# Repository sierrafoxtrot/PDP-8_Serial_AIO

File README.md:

# PDP-8 Serial All-in-One

A W070 compatible serial interface for the original DEC PDP-8, providing both teletype current loop and RS-232 compatible interfaces.

## Background

The original PDP-8 was commonly used with an ASR-33 Teletype connected through a DEC W070 interface. The ASR-33 provided a 110 baud printing terminal together with paper tape punch and reader facilities.

The Australian Computer Museum Society PDP-8 is missing its W070 interface. This project started as a [RetroChallenge 2026/10](https://www.retrochallenge.org/) project to build a practical replacement, while adding an RS-232 interface so the machine can also be used with terminals such as a DECWriter or VT220, or with a modern computer through a USB to RS-232 adaptor.

[RetroChallenge 2026/10 project thread](https://forum.acms.org.au/t/rc2026-10-pdp-8-serial-interface/1152)

## Design goals

* Provide a functional replacement for the serial and current loop functions of the DEC W070.
* Retain support for a period current loop Teletype, including reader enable.
* Provide an RS-232 DCE interface on a DE-9 connector.
* Allow the PDP-8 transmit, receive and reader enable paths to be independently selected between current loop and RS-232.
* Preserve the PDP-8 negative logic interface levels.
* Provide visible TX, RX and Reader Enable status indicators.
* Use straightforward, readily available components and remain practical to diagnose and repair.

There is deliberately no onboard USB interface. A conventional RS-232 interface keeps the board useful with both period equipment and modern USB to RS-232 adaptors. I've compromised on going with the the more 1980's era DE-9 connector to accomodate the screw terminals for the current loop.

## Interfaces

### W070 compatible current loop

The six position terminal block provides the Teletype connections:

| Terminal | Connection |
| ---: | --- |
| 1 | TTI return |
| 2 | TTO |
| 3 | TTI, -15 V |
| 4 | Reader, +10 V |
| 5 | Reader enable |
| 6 | TTO return |

The connections are arranged as three pairs:

* **TTI / keyboard:** 3 (-15 V), 1 (return)
* **TTO / printer:** 2 (TTO), 6 (return)
* **Reader enable:** 4 (+10 V), 5 (enable)

### RS-232

The DE-9 connector is wired as **DCE** and is intended for use with a straight through cable to a DTE terminal or computer. If you are using a USB-RS232 adaptor, it should plug in directly.

| Pin | Function |
| ---: | --- |
| 2 | TX |
| 3 | RX |
| 5 | GND |
| 8 | CTS / Reader Enable |

### Interface selection

Three selector links choose the interface used for the relevant PDP-8 signals:

| Link position | Interface |
| --- | --- |
| 1 to 2 | RS-232 |
| 2 to 3 | Current loop |

### Indicators

* **TX** indicates transmitted SPACE states.
* **RX** indicates received SPACE states.
* **RE** indicates Reader Enable.

## Power

The board uses the supplies already available in the PDP-8:

* +10 V
* -15 V
* GND

A local 78L05 regulator provides the +5 V supply required by the interface logic.

## Design files

The project is designed in [KiCad](https://www.kicad.org/). The repository contains the schematic, PCB layout and associated project files required to reproduce or modify the board.

Before manufacturing a board, check the current revision notes and run KiCad ERC and DRC. As with any interface connected to vintage hardware, verify supply voltages and connector wiring before installation.

## Licence

This hardware design is licensed under the **CERN Open Hardware Licence Version 2, Weakly Reciprocal**.

SPDX-License-Identifier: `CERN-OHL-W-2.0`

See [LICENSE](LICENSE) for the full licence text.

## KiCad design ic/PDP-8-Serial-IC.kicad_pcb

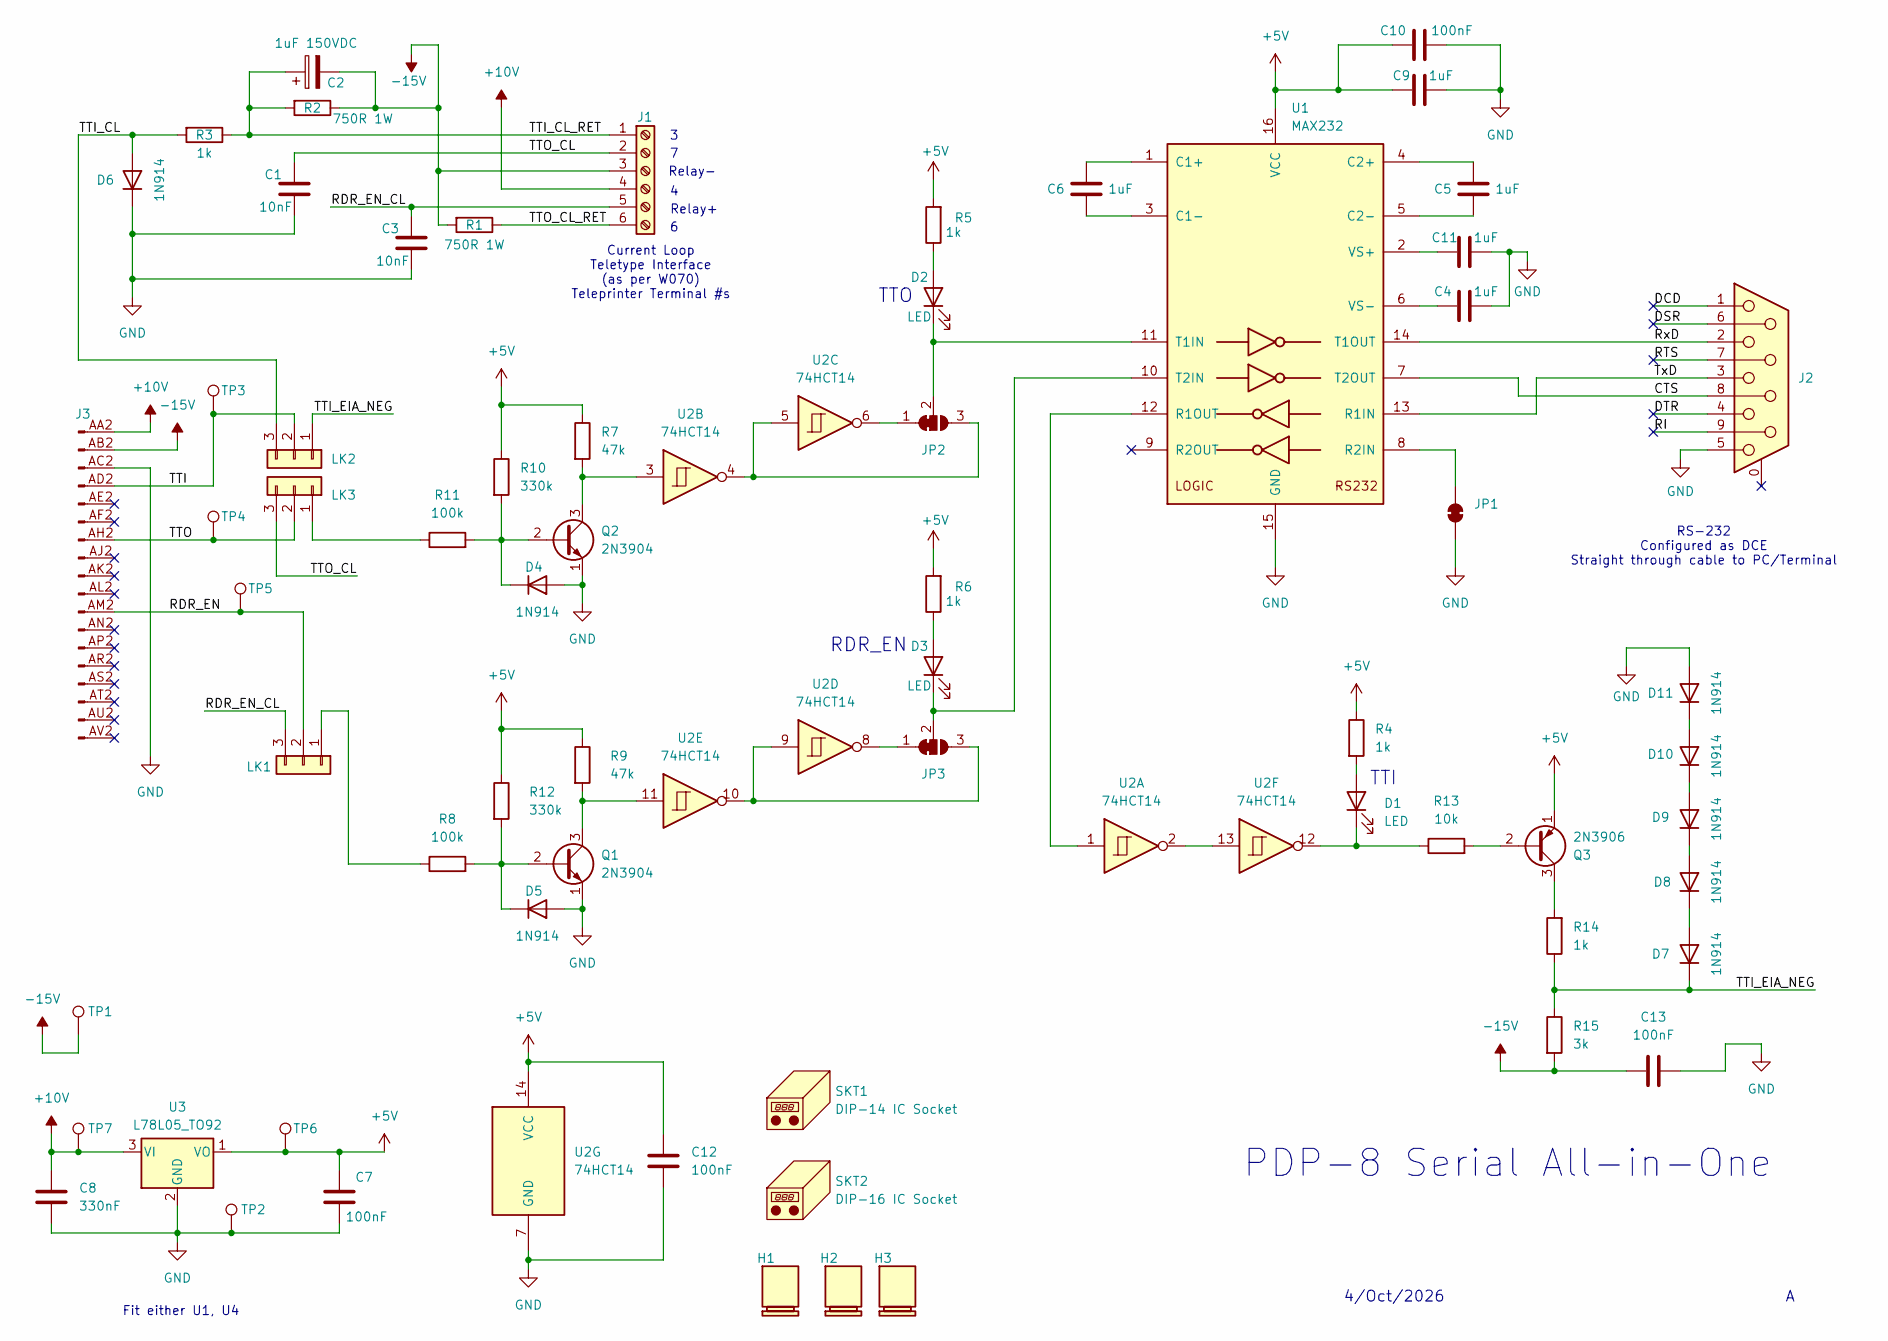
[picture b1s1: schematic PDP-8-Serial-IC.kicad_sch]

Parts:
C1, C3: 10nF; C_Disc_D5.0mm_W2.5mm_P2.50mm; MPN RDER71H103K0K1H03B; Digikey_PN 490-8812-ND
C2: 1uF 150VDC; CP_Axial_L29.0mm_D13.0mm_P35.00mm_Horizontal; MPN MKP1839510254; Digikey_PN 2870-MKP1839510254-ND
C4, C5, C6, C9, C11: 1uF; C_Disc_D5.0mm_W2.5mm_P5.00mm; MPN RDER71H105K2K1H03B; Digikey_PN 490-8816-ND
C7, C10, C12, C13: 100nF; C_Disc_D5.0mm_W2.5mm_P2.50mm; MPN RDER71H104K0S1H03A; Digikey_PN 490-9145-1-ND
C8: 330nF; C_Disc_D5.0mm_W2.5mm_P5.00mm; MPN FA14X7R1H334KNU06; Digikey_PN 445-180408-1-ND
D1, D2, D3: LED; LED_D3.0mm; MPN LTL1CHKEKNN; Digikey_PN 160-1943-ND
D4, D5, D6, D7, D8, D9, D10, D11: 1N914; D_DO-35_SOD27_P7.62mm_Horizontal; MPN 1N914B; Digikey_PN 1N914B-ND
H1, H2, H3: Jumper_Shunt; MPN QPC02SXGN-RC; DigiKey_PN S9337-ND
J1: Screw_Terminal_01x06; PhoenixContact_MC_1,5_6-G-3.5_1x06_P3.50mm_Horizontal
J2: DE9_Socket_MountingHoles; DSUB-9_Pins_Horizontal_P2.77x2.84mm_EdgePinOffset7.70mm_Hou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; MPN A-DF 09 A/KG-T2S; Digikey_PN AE10921-ND
J3: FlipChip_01x18; DEC_single_short_holeless
JP1: SolderJumper_2_Bridged; SolderJumper-2_P1.3mm_Bridged2Bar_RoundedPad1.0x1.5mm
JP2, JP3: SolderJumper_3_Bridged12; SolderJumper-3_P1.3mm_Bridged2Bar12_RoundedPad1.0x1.5mm_Num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
LK1, LK2, LK3: Conn_01x03; PinHeader_1x03_P2.54mm_Vertical; MPN PREC003SAAAN-RC; Digikey_PN S1012EC-03-ND
Q1, Q2: 2N3904; TO-92_Inline; MPN 2N3904BU; Digikey_PN 2N3904FS-ND
Q3: 2N3906; TO-92_Inline; MPN 2N3906BU; Digikey_PN 2N3906FS-ND
R1, R2: 750R 1W; R_Axial_DIN0414_L11.9mm_D4.5mm_P20.32mm_Horizontal; MPN RSF100JB-73-750R; Digikey_PN 13-RSF100JB-73-750R-ND
R3, R4, R5, R6, R14: 1k; R_Axial_DIN0207_L6.3mm_D2.5mm_P10.16mm_Horizontal; MPN MFR-25FBF52-1K; Digikey_PN 1.00KXBK-ND
R7, R9: 47k; R_Axial_DIN0207_L6.3mm_D2.5mm_P10.16mm_Horizontal; MPN RES 47K OHM 1% 1/4W AXIAL; Digikey_PN MFR-25FBF52-47K-ND
R8, R11: 100k; R_Axial_DIN0207_L6.3mm_D2.5mm_P10.16mm_Horizontal; MPN MFR-25FBF52-100K; Digikey_PN 100KXBK-ND
R10, R12: 330k; R_Axial_DIN0207_L6.3mm_D2.5mm_P10.16mm_Horizontal; MPN MFR-25FBF52-330K; Digikey_PN MFR-25FBF52-330K-ND
R13: 10k; R_Axial_DIN0207_L6.3mm_D2.5mm_P10.16mm_Horizontal; MPN MFR-25FBF52-10K; Digikey_PN 10.0KXBK-ND
R15: 3k; R_Axial_DIN0207_L6.3mm_D2.5mm_P10.16mm_Horizontal; MPN MFR-25FBF52-3K; Digikey_PN 13-MFR-25FBF52-3K-ND
SKT1: DIP-14 IC Socket; MPN A 14-LC-TT; Digikey_PN AE9989-ND
SKT2: DIP-16 IC Socket; MPN A 16-LC-TT; Digikey_PN AE9992-ND
TP1: -15V; TestPoint_Loop_D3.50mm_Drill0.9mm_Beaded
TP2: GND; TestPoint_Loop_D3.50mm_Drill0.9mm_Beaded
TP3: TTI; TestPoint_Loop_D3.50mm_Drill0.9mm_Beaded
TP4: TTO; TestPoint_Loop_D3.50mm_Drill0.9mm_Beaded
TP5: RDR_EN; TestPoint_Loop_D3.50mm_Drill0.9mm_Beaded
TP6: +5V; TestPoint_Loop_D3.50mm_Drill0.9mm_Beaded
TP7: +10V; TestPoint_Loop_D3.50mm_Drill0.9mm_Beaded
U1: MAX232; DIP-16_W7.62mm; MPN MAX232EIN; Digikey_PN 296-27963-5-ND
U2: 74HCT14; DIP-14_W7.62mm; MPN SN74HCT14N; Digikey_PN 296-8394-5-ND
U3: L78L05_TO92; TO-92_Inline; MPN L78L05ACZ; Digikey_PN 497-2952-ND

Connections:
+5V: C7.1, C9.1, C10.1, C12.1, Q3.1 (E), R4.1, R5.2, R6.2, R7.1, R9.1, R10.1, R12.1, TP6.1, U1.16 (VCC), U2.14 (VCC), U3.1 (VO)
+10V: C8.1, J1.4, J3.AA2 (Pin_A), TP7.1, U3.3 (VI)
-15V: C2.2, C13.1, J1.3, J3.AB2 (Pin_B), R1.2, R2.1, R15.2, TP1.1
/CTS: J2.8, U1.7 (T2OUT)
/DCD: J2.1
/DSR: J2.6
/DTR: J2.4
/RDR_EN: J3.AM2 (Pin_M), LK1.2, TP5.1
/RDR_EN_CL: C3.1, J1.5, LK1.3
/RI: J2.9
/RTS: J2.7
/RxD: J2.2, U1.14 (T1OUT)
/TTI: J3.AD2 (Pin_D), LK2.2, TP3.1
/TTI_CL: D6.2 (A), LK2.3, R3.2
/TTI_CL_RET: C2.1, J1.1, R2.2, R3.1
/TTI_EIA_NEG: D7.1 (K), LK2.1, R14.1, R15.1
/TTO: J3.AH2 (Pin_H), LK3.2, TP4.1
/TTO_CL: C1.1, J1.2, LK3.3
/TTO_CL_RET: J1.6, R1.1
/TxD: J2.3, U1.13 (R1IN)
GND: C1.2, C3.2, C4.2, C7.2, C8.2, C9.2, C10.2, C11.2, C12.2, C13.2, D4.2 (A), D5.2 (A), D6.1 (K), D11.2 (A), J2.5, J3.AC2 (Pin_C), JP1.2 (B), Q1.1 (E), Q2.1 (E), TP2.1, U1.15 (GND), U2.7 (GND), U3.2 (GND)
unnamed: D1.2 (A), R4.2
unnamed: D1.1 (K), R13.1, U2.12
unnamed: D2.2 (A), R5.1
unnamed: D2.1 (K), JP2.2 (C), U1.11 (T1IN)
unnamed: D3.2 (A), R6.1
unnamed: D3.1 (K), JP3.2 (C), U1.10 (T2IN)
unnamed: D4.1 (K), Q2.2 (B), R10.2, R11.2
unnamed: D5.1 (K), Q1.2 (B), R8.2, R12.2
unnamed: D7.2 (A), D8.1 (K)
unnamed: D8.2 (A), D9.1 (K)
unnamed: D10.2 (A), D11.1 (K)
unnamed: D9.2 (A), D10.1 (K)
unnamed: JP1.1 (A), U1.8 (R2IN)
unnamed: JP2.1 (A), U2.6
unnamed: JP2.3 (B), U2.4, U2.5
unnamed: JP3.1 (A), U2.8
unnamed: JP3.3 (B), U2.9, U2.10
unnamed: LK1.1, R8.1
unnamed: LK3.1, R11.1
unnamed: Q1.3 (C), R9.2, U2.11
unnamed: Q2.3 (C), R7.2, U2.3
unnamed: Q3.2 (B), R13.2
unnamed: Q3.3 (C), R14.2
unnamed: C6.2, U1.1 (C1+)
unnamed: C6.1, U1.3 (C1-)
unnamed: C5.2, U1.4 (C2+)
unnamed: C5.1, U1.5 (C2-)
unnamed: U1.12 (R1OUT), U2.1
unnamed: C11.1, U1.2 (VS+)
unnamed: C4.1, U1.6 (VS-)
unnamed: U2.2, U2.13

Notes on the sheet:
Relay-
TTI
Relay+
Fit either U1, U4
PDP-8 Serial All-in-One
RS-232 Configured as DCE Straight through cable to PC/Terminal
4/Oct/2026
Current Loop Teletype Interface (as per W070) Teleprinter Terminal #s
RDR_EN
TTO

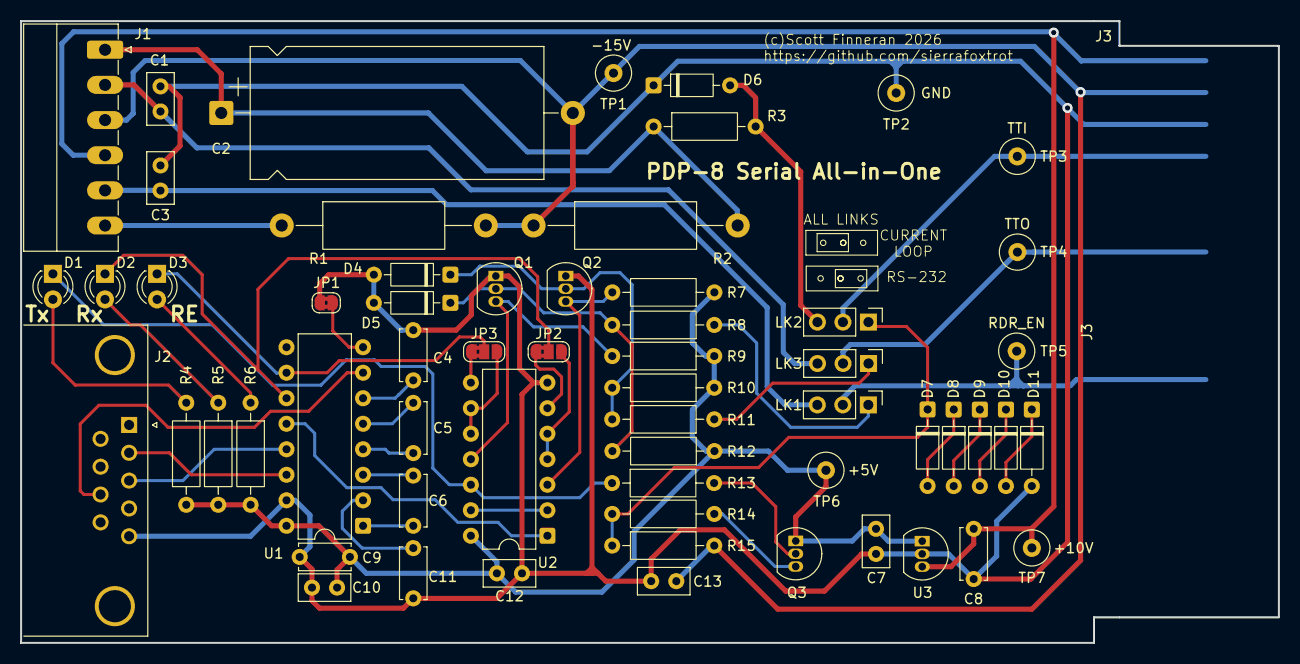
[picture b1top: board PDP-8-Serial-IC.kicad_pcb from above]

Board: 2 copper layers, 125.2 x 61.9 mm, 61 parts (0 on the bottom side), 47 nets.

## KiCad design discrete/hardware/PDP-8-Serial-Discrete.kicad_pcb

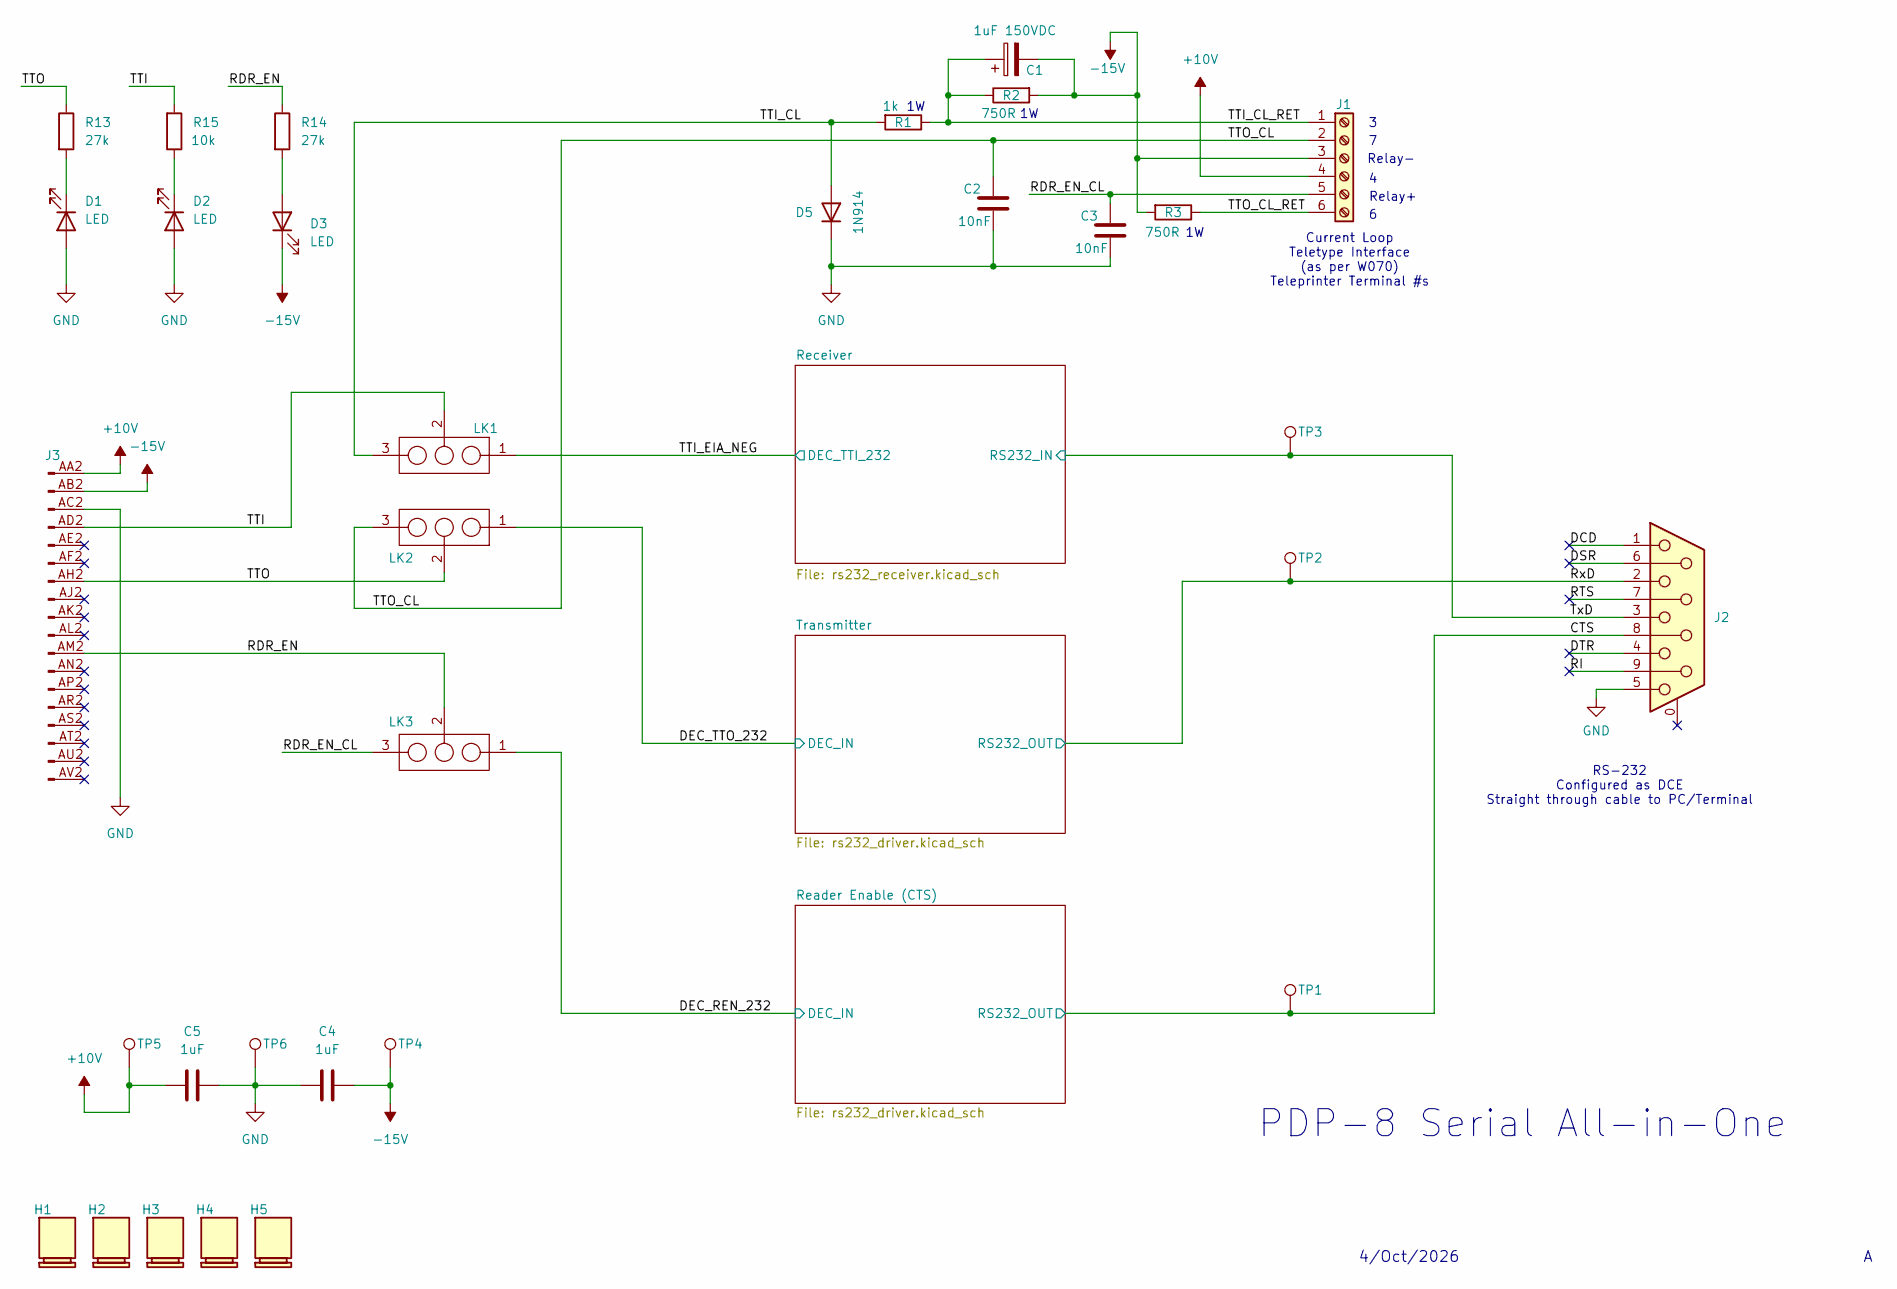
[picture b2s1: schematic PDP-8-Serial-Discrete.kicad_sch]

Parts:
C1: 1uF 150VDC; CP_Axial_L29.0mm_D13.0mm_P35.00mm_Horizontal; MPN MKP1839510254; DigiKey_PN 2870-MKP1839510254-ND
C2, C3: 10nF; C_Disc_D5.0mm_W2.5mm_P2.50mm; MPN RDER71H103K0K1H03B; DigiKey_PN 490-8812-ND
C4, C5: 1uF; C_Disc_D5.0mm_W2.5mm_P5.00mm; MPN RDER71H105K2K1H03B; DigiKey_PN 490-8816-ND
D1, D2, D3: LED; LED_D3.0mm; MPN LTL1CHKEKNN; DigiKey_PN 160-1943-ND
D5: 1N914; D_DO-35_SOD27_P7.62mm_Horizontal; MPN 1N914B; DigiKey_PN 1N914B-ND
H1, H2, H3, H4, H5: Jumper_Shunt; MPN QPC02SXGN-RC; DigiKey_PN S9337-ND
J1: Screw_Terminal_01x06; PhoenixContact_MC_1,5_6-G-3.5_1x06_P3.50mm_Horizontal
J2: DE9_Socket_MountingHoles; DSUB-9_Pins_Horizontal_P2.77x2.84mm_EdgePinOffset7.70mm_Hou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; MPN A-DF 09 A/KG-T2S; DigiKey_PN AE10921-ND
J3: FlipChip_01x18; DEC_single_short_holeless
LK1, LK2, LK3: Link_01x03; PinHeader_1x03_P2.54mm_Vertical; MPN PREC003SAAAN-RC; DigiKey_PN S1012EC-03-ND
R1: 1k; R_Axial_DIN0414_L11.9mm_D4.5mm_P20.32mm_Horizontal; MPN MFR-25FBF52-1K; DigiKey_PN 1.00KXBK-ND
R2, R3: 750R; R_Axial_DIN0414_L11.9mm_D4.5mm_P20.32mm_Horizontal; MPN RSF100JB-73-750R; DigiKey_PN 13-RSF100JB-73-750R-ND
R13, R14: 27k; R_Axial_DIN0207_L6.3mm_D2.5mm_P7.62mm_Horizontal; MPN RES 27K OHM 1% 1/4W AXIAL; DigiKey_PN MFR-25FBF52-27K-ND
R15: 10k; R_Axial_DIN0207_L6.3mm_D2.5mm_P7.62mm_Horizontal; MPN MFR-25FBF52-10K; DigiKey_PN 10.0KXBK-ND
TP1: CTS; TestPoint_Loop_D3.50mm_Drill0.9mm_Beaded
TP2: RxD; TestPoint_Loop_D3.50mm_Drill0.9mm_Beaded
TP3: TxD; TestPoint_Loop_D3.50mm_Drill0.9mm_Beaded
TP4: -15V; TestPoint_Loop_D3.50mm_Drill0.9mm_Beaded
TP5: +10V; TestPoint_Loop_D3.50mm_Drill0.9mm_Beaded
TP6: GND; TestPoint_Loop_D3.50mm_Drill0.9mm_Beaded

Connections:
+10V: C5.1, J1.4, J3.AA2 (Pin_A), TP5.1; also elsewhere on the board
-15V: C1.2, C4.1, D3.1 (K), J1.3, J3.AB2 (Pin_B), R2.2, R3.2, TP4.1; also elsewhere on the board
/CTS: J2.8, TP1.1; also elsewhere on the board
/DCD: J2.1
/DEC_REN_232: LK3.1; also elsewhere on the board
/DEC_TTO_232: LK2.1; also elsewhere on the board
/DSR: J2.6
/DTR: J2.4
/RDR_EN: J3.AM2 (Pin_M), LK3.2, R14.1
/RDR_EN_CL: C3.1, J1.5, LK3.3
/RI: J2.9
/RTS: J2.7
/RxD: J2.2, TP2.1; also elsewhere on the board
/TTI: J3.AD2 (Pin_D), LK1.2, R15.2
/TTI_CL: D5.2 (A), LK1.3, R1.2
/TTI_CL_RET: C1.1, J1.1, R1.1, R2.1
/TTI_EIA_NEG: LK1.1; also elsewhere on the board
/TTO: J3.AH2 (Pin_H), LK2.2, R13.1
/TTO_CL: C2.1, J1.2, LK2.3
/TTO_CL_RET: J1.6, R3.1
/TxD: J2.3, TP3.1; also elsewhere on the board
GND: C2.2, C3.2, C4.2, C5.2, D1.2 (A), D2.2 (A), D5.1 (K), J2.5, J3.AC2 (Pin_C), TP6.1; also elsewhere on the board
unnamed: D1.1 (K), R13.2
unnamed: D2.1 (K), R15.1
unnamed: D3.2 (A), R14.2

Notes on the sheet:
Relay-
Relay+
PDP-8 Serial All-in-One
RS-232 Configured as DCE Straight through cable to PC/Terminal
4/Oct/2026
Current Loop Teletype Interface (as per W070) Teleprinter Terminal #s

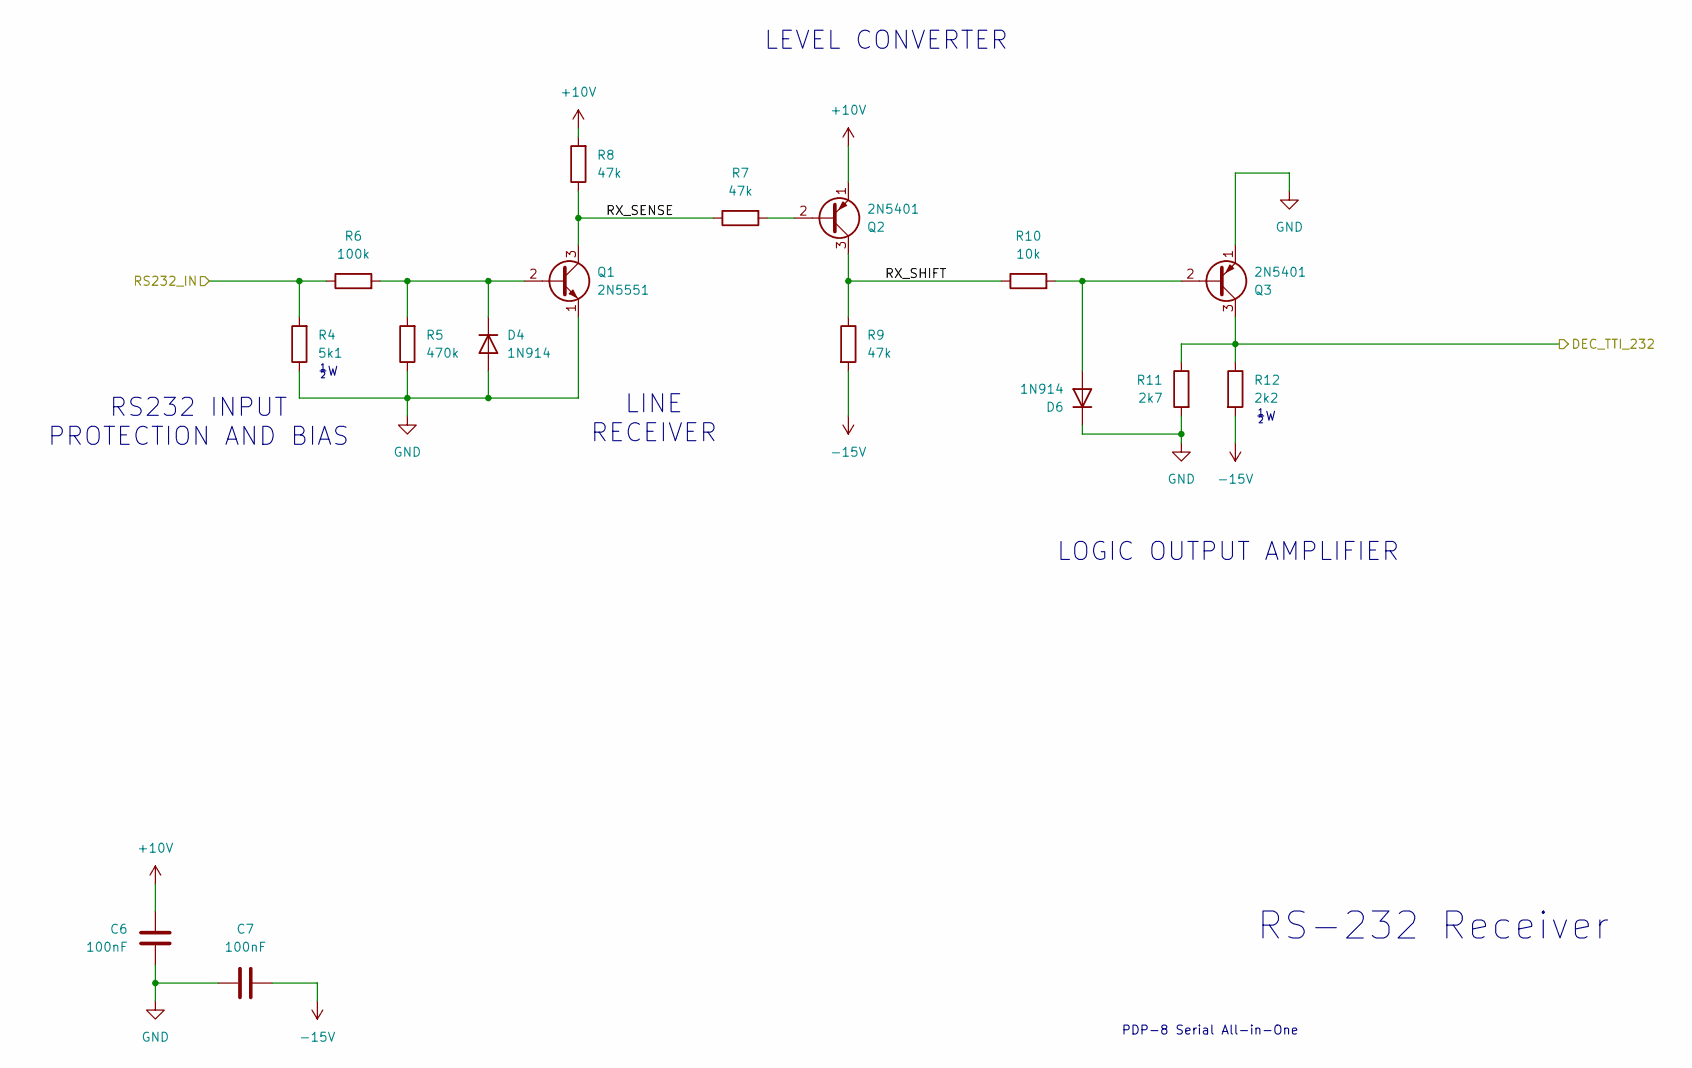
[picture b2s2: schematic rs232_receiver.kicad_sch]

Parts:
C6, C7: 100nF; C_Disc_D5.0mm_W2.5mm_P2.50mm; MPN RDER71H104K0S1H03A; DigiKey_PN 490-9145-1-ND
D4, D6: 1N914; D_DO-35_SOD27_P7.62mm_Horizontal; MPN 1N914B; DigiKey_PN 1N914B-ND
Q1: 2N5551; TO-92_Inline; MPN 2N5551; DigiKey_PN 4878-2N5551CT-ND
Q2, Q3: 2N5401; TO-92_Inline; MPN 2N5401; DigiKey_PN 4878-2N5401CT-ND
R4: 5k1; R_Axial_DIN0309_L9.0mm_D3.2mm_P12.70mm_Horizontal; MPN MFR-50FRF52-5K1; DigiKey_PN 13-MFR50SFTE52-5K1CT-ND
R5: 470k; R_Axial_DIN0207_L6.3mm_D2.5mm_P7.62mm_Horizontal; MPN MFR-25FBF52-470K; DigiKey_PN MFR-25FBF52-470K-ND
R6: 100k; R_Axial_DIN0207_L6.3mm_D2.5mm_P7.62mm_Horizontal; MPN MFR-25FBF52-100K; DigiKey_PN 100KXBK-ND
R7, R8, R9: 47k; R_Axial_DIN0207_L6.3mm_D2.5mm_P7.62mm_Horizontal; MPN RES 47K OHM 1% 1/4W AXIAL; DigiKey_PN MFR-25FBF52-47K-ND
R10: 10k; R_Axial_DIN0207_L6.3mm_D2.5mm_P7.62mm_Horizontal; MPN MFR-25FBF52-10K; DigiKey_PN 10.0KXBK-ND
R11: 2k7; R_Axial_DIN0207_L6.3mm_D2.5mm_P7.62mm_Horizontal; MPN RES 2.7K OHM 1% 1/4W AXIAL; DigiKey_PN MFR-25FBF52-2K7-ND
R12: 2k2; R_Axial_DIN0309_L9.0mm_D3.2mm_P12.70mm_Horizontal; MPN MFR50SFTE52-2K2; DigiKey_PN 13-MFR50SFTE52-2K2CT-ND

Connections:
+10V: C6.1, Q2.1 (E), R8.2; also elsewhere on the board
-15V: C7.2, R9.2, R12.2; also elsewhere on the board
/Receiver/RX_SENSE: Q1.3 (C), R7.1, R8.1
/Receiver/RX_SHIFT: Q2.3 (C), R9.1, R10.1
/TTI_EIA_NEG: Q3.3 (C), R11.1, R12.1; also elsewhere on the board
/TxD: R4.2, R6.1; also elsewhere on the board
GND: C6.2, C7.1, D4.2 (A), D6.1 (K), Q1.1 (E), Q3.1 (E), R4.1, R5.1, R11.2; also elsewhere on the board
unnamed: D4.1 (K), Q1.2 (B), R5.2, R6.2
unnamed: D6.2 (A), Q3.2 (B), R10.2
unnamed: Q2.2 (B), R7.2

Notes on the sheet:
LEVEL CONVERTER
RS-232 Receiver
PDP-8 Serial All-in-One
RS232 INPUT PROTECTION AND BIAS
LOGIC OUTPUT AMPLIFIER
LINE RECEIVER

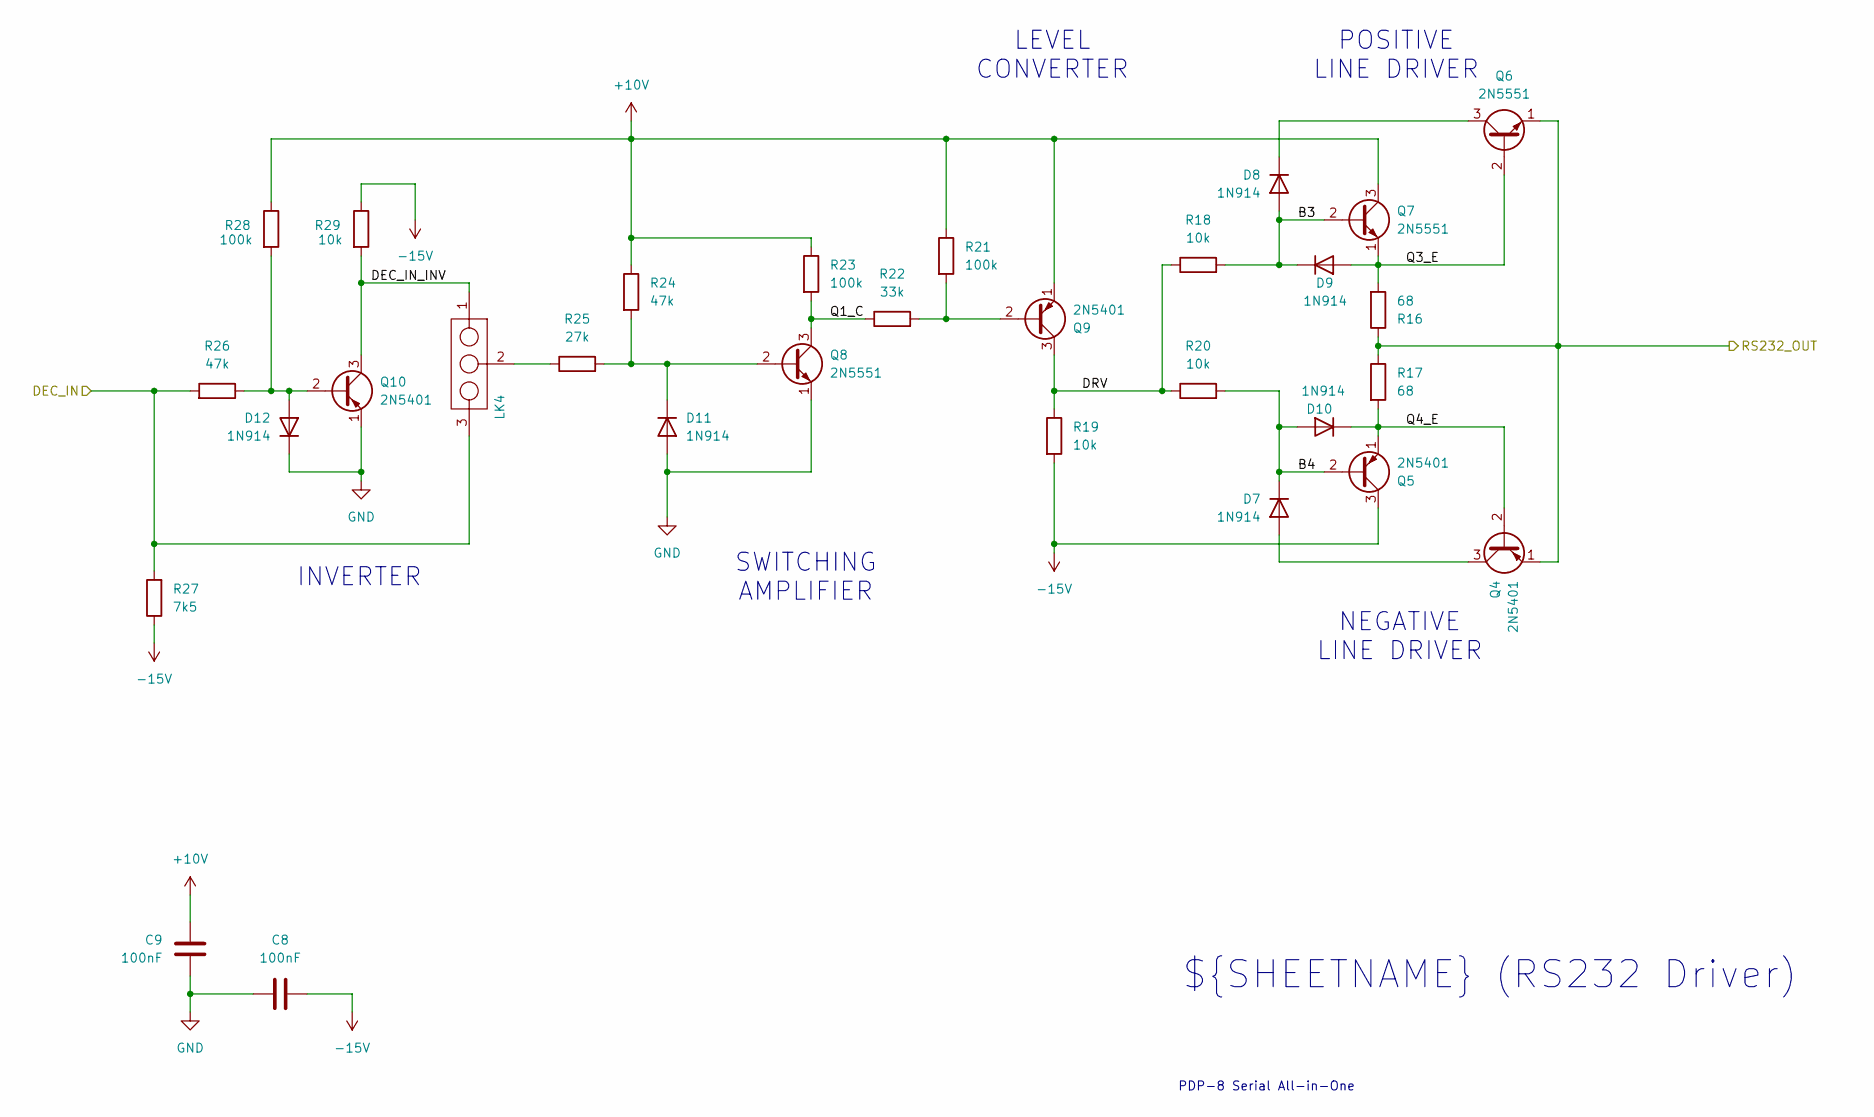
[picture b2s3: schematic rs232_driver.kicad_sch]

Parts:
C8, C9: 100nF; C_Disc_D5.0mm_W2.5mm_P2.50mm; MPN RDER71H104K0S1H03A; DigiKey_PN 490-9145-1-ND
D7, D8, D9, D10, D11, D12: 1N914; D_DO-35_SOD27_P7.62mm_Horizontal; MPN 1N914B; DigiKey_PN 1N914B-ND
LK4: Link_01x03; PinHeader_1x03_P2.54mm_Vertical; MPN PREC003SAAAN-RC; DigiKey_PN S1012EC-03-ND
Q4, Q5, Q9, Q10: 2N5401; TO-92_Inline; MPN 2N5401; DigiKey_PN 4878-2N5401CT-ND
Q6, Q7, Q8: 2N5551; TO-92_Inline; MPN 2N5551; DigiKey_PN 4878-2N5551CT-ND
R16, R17: 68; R_Axial_DIN0207_L6.3mm_D2.5mm_P7.62mm_Horizontal; MPN RES 68 OHM 1% 1/4W AXIAL; DigiKey_PN 13-MFR-25FBF52-68R-ND
R18, R19, R20, R29: 10k; R_Axial_DIN0207_L6.3mm_D2.5mm_P7.62mm_Horizontal; MPN MFR-25FBF52-10K; DigiKey_PN 10.0KXBK-ND
R21, R23, R28: 100k; R_Axial_DIN0207_L6.3mm_D2.5mm_P7.62mm_Horizontal; MPN MFR-25FBF52-100K; DigiKey_PN 100KXBK-ND
R22: 33k; R_Axial_DIN0207_L6.3mm_D2.5mm_P7.62mm_Horizontal; MPN MFR-25FBF52-33K; DigiKey_PN RES 68 OHM 1% 1/4W AXIAL
R24, R26: 47k; R_Axial_DIN0207_L6.3mm_D2.5mm_P7.62mm_Horizontal; MPN RES 47K OHM 1% 1/4W AXIAL; DigiKey_PN MFR-25FBF52-47K-ND
R25: 27k; R_Axial_DIN0207_L6.3mm_D2.5mm_P7.62mm_Horizontal; MPN RES 27K OHM 1% 1/4W AXIAL; DigiKey_PN MFR-25FBF52-27K-ND
R27: 7k5; R_Axial_DIN0207_L6.3mm_D2.5mm_P7.62mm_Horizontal; MPN RES 7.5K OHM 1% 1/4W AXIAL; DigiKey_PN 7.50KXBK-ND

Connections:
+10V: C9.1, Q7.3 (C), Q9.1 (E), R21.1, R23.1, R24.1, R28.1; also elsewhere on the board
-15V: C8.2, Q5.3 (C), R19.2, R27.1, R29.1; also elsewhere on the board
/DEC_TTO_232: LK4.3, R26.2, R27.2; also elsewhere on the board
/RxD: Q4.1 (E), Q6.1 (E), R16.1, R17.1; also elsewhere on the board
/Transmitter/B3: D8.2 (A), D9.1 (K), Q7.2 (B), R18.2
/Transmitter/B4: D7.1 (K), D10.2 (A), Q5.2 (B), R20.2
/Transmitter/DEC_IN_INV: LK4.1, Q10.3 (C), R29.2
/Transmitter/DRV: Q9.3 (C), R18.1, R19.1, R20.1
/Transmitter/Q1_C: Q8.3 (C), R22.1, R23.2
/Transmitter/Q3_E: D9.2 (A), Q6.2 (B), Q7.1 (E), R16.2
/Transmitter/Q4_E: D10.1 (K), Q4.2 (B), Q5.1 (E), R17.2
GND: C8.1, C9.2, D11.2 (A), D12.1 (K), Q8.1 (E), Q10.1 (E); also elsewhere on the board
unnamed: D7.2 (A), Q4.3 (C)
unnamed: D8.1 (K), Q6.3 (C)
unnamed: D11.1 (K), Q8.2 (B), R24.2, R25.2
unnamed: D12.2 (A), Q10.2 (B), R26.1, R28.2
unnamed: LK4.2, R25.1
unnamed: Q9.2 (B), R21.2, R22.2

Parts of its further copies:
C10, C11: 100nF; C_Disc_D5.0mm_W2.5mm_P2.50mm; MPN RDER71H104K0S1H03A; DigiKey_PN 490-9145-1-ND
D13, D14, D15, D16, D17, D18: 1N914; D_DO-35_SOD27_P7.62mm_Horizontal; MPN 1N914B; DigiKey_PN 1N914B-ND
LK5: Link_01x03; PinHeader_1x03_P2.54mm_Vertical; MPN PREC003SAAAN-RC; DigiKey_PN S1012EC-03-ND
Q11, Q12, Q16, Q17: 2N5401; TO-92_Inline; MPN 2N5401; DigiKey_PN 4878-2N5401CT-ND
Q13, Q14, Q15: 2N5551; TO-92_Inline; MPN 2N5551; DigiKey_PN 4878-2N5551CT-ND
R30, R31: 68; R_Axial_DIN0207_L6.3mm_D2.5mm_P7.62mm_Horizontal; MPN RES 68 OHM 1% 1/4W AXIAL; DigiKey_PN 13-MFR-25FBF52-68R-ND
R32, R33, R34, R42: 10k; R_Axial_DIN0207_L6.3mm_D2.5mm_P7.62mm_Horizontal; MPN MFR-25FBF52-10K; DigiKey_PN 10.0KXBK-ND
R35: 33k; R_Axial_DIN0207_L6.3mm_D2.5mm_P7.62mm_Horizontal; MPN MFR-25FBF52-33K; DigiKey_PN RES 68 OHM 1% 1/4W AXIAL
R36, R37, R43: 100k; R_Axial_DIN0207_L6.3mm_D2.5mm_P7.62mm_Horizontal; MPN MFR-25FBF52-100K; DigiKey_PN 100KXBK-ND
R38, R41: 47k; R_Axial_DIN0207_L6.3mm_D2.5mm_P7.62mm_Horizontal; MPN RES 47K OHM 1% 1/4W AXIAL; DigiKey_PN MFR-25FBF52-47K-ND
R39: 27k; R_Axial_DIN0207_L6.3mm_D2.5mm_P7.62mm_Horizontal; MPN RES 27K OHM 1% 1/4W AXIAL; DigiKey_PN MFR-25FBF52-27K-ND
R40: 7k5; R_Axial_DIN0207_L6.3mm_D2.5mm_P7.62mm_Horizontal; MPN RES 7.5K OHM 1% 1/4W AXIAL; DigiKey_PN 7.50KXBK-ND

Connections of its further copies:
+10V: C11.1, Q14.3 (C), Q16.1 (E), R36.1, R37.1, R38.1, R43.1; also elsewhere on the board
-15V: C10.2, Q12.3 (C), R33.2, R40.1, R42.1; also elsewhere on the board
/CTS: Q11.1 (E), Q13.1 (E), R30.1, R31.1; also elsewhere on the board
/DEC_REN_232: LK5.3, R40.2, R41.2; also elsewhere on the board
/Reader Enable (CTS)/B3: D14.1 (K), D15.2 (A), Q14.2 (B), R32.2
/Reader Enable (CTS)/B4: D13.1 (K), D16.2 (A), Q12.2 (B), R34.2
/Reader Enable (CTS)/DEC_IN_INV: LK5.1, Q17.3 (C), R42.2
/Reader Enable (CTS)/DRV: Q16.3 (C), R32.1, R33.1, R34.1
/Reader Enable (CTS)/Q1_C: Q15.3 (C), R35.1, R37.2
/Reader Enable (CTS)/Q3_E: D14.2 (A), Q13.2 (B), Q14.1 (E), R31.2
/Reader Enable (CTS)/Q4_E: D16.1 (K), Q11.2 (B), Q12.1 (E), R30.2
GND: C10.1, C11.2, D17.2 (A), D18.1 (K), Q15.1 (E), Q17.1 (E); also elsewhere on the board
unnamed: D13.2 (A), Q11.3 (C)
unnamed: D15.1 (K), Q13.3 (C)
unnamed: D17.1 (K), Q15.2 (B), R38.2, R39.2
unnamed: D18.2 (A), Q17.2 (B), R41.1, R43.2
unnamed: LK5.2, R39.1
unnamed: Q16.2 (B), R35.2, R36.2

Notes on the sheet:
${SHEETNAME} (RS232 Driver)
NEGATIVE LINE DRIVER
LEVEL CONVERTER
POSITIVE LINE DRIVER
SWITCHING AMPLIFIER
INVERTER
PDP-8 Serial All-in-One

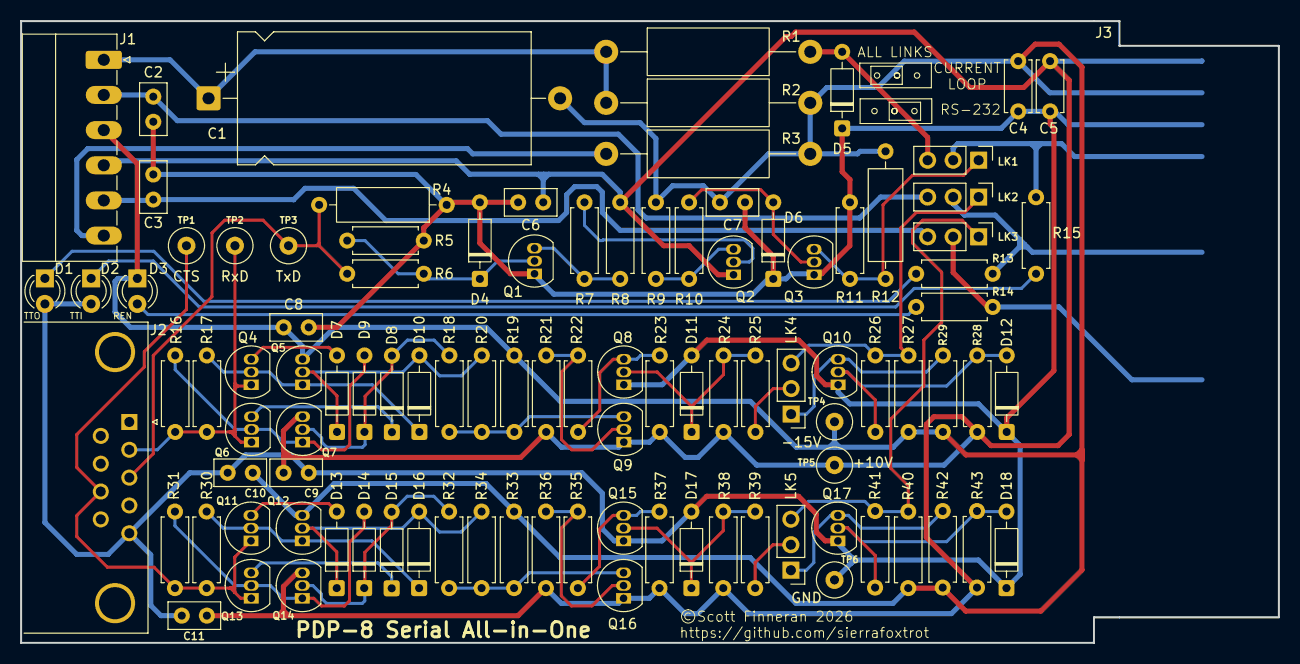
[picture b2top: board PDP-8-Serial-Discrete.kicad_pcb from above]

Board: 2 copper layers, 125.2 x 61.9 mm, 103 parts (0 on the bottom side), 51 nets.

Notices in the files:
discrete/hardware/PDP-8-Serial-Discrete.kicad_pcb:
©Scott Finneran 2026
